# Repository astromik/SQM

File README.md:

<B>Amatérské SQM - Sky Quality Meter</B><br><br>Levnější a funkčně více vybavená náhrada za profesionální měřič kvality oblohy od Unihedronu postavená na procesoru STM32F411CEU s využitím modulu pro měření jasu TSL2591.

- Záznamy se ukládají na SD kartu (čitelný CSV formát) a do vnitřní EEPROM, ze které je možné záznamy exporovat.<br>
- Měření teploty, tlaku a vlhkosti.<br>
- K záznamům se přidávají GPS souřadnice a směr měření (azimut a  elevace).<br>
- Astronomické výpočty (poloha Slunce, Měsíce, planet, vybrané DSO).<br>
- Komunikace přes RS485 (modbus), nebo přes USB.<br>
- Možnost automatického měření v nastavených intervalech.<br>
- Další drobné funkce (stopky, budík, časová značka, červená lampička, GPX trasovací soubor).<br>
- Kalibrace pomocí porovnání s originálním (přesným) SQM přes editovatelné kalibrační tabulky.

Web: http://sqm.astromik.org/<br><br>

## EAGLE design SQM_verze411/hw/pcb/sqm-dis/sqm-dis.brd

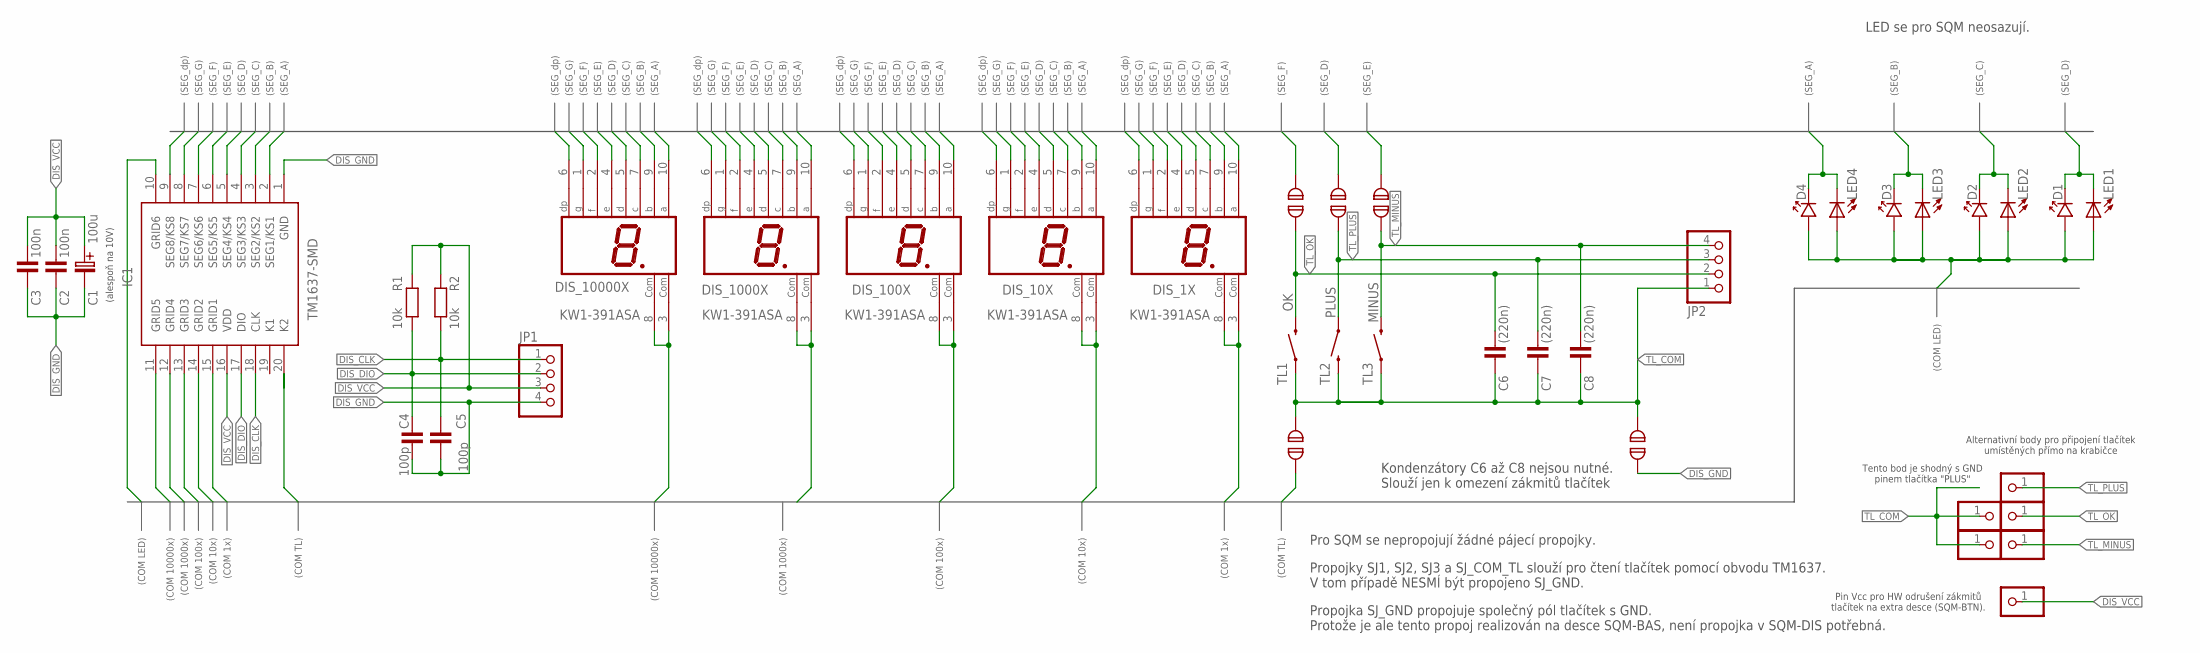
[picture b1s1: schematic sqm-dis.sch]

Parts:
C1: 100u; C-EL_2,5
C2, C3: 100n; 0805
C4, C5: 100p; 0805
C6, C7, C8: (220n); 0805
D1, D2, D3, D4: LED_3
DIS_1X, DIS_10X, DIS_100X, DIS_1000X, DIS_10000X: KW1-391ASA; HDSP-E
IC1: TM1637-SMD; SOIC127P1045X280-20N
JP1, JP2: PINHD-1X4; 1X04
JP3, JP4, JP5, JP6, JP7, JP8: PINHD-1X1; 1X01
LED1, LED2, LED3, LED4: LEDCHIP-LED0805; CHIP-LED0805
R1, R2: 10k; 0805
SJ1, SJ2, SJ3: SJ; SJ_2S-NO
SJ_COM_TL: SJ; SJ_2S-NO
SJ_GND: SJ; SJ_2S-NO
TL1: OK; TACTILE_SWITCH_PTH_6.0MM
TL2: PLUS; TACTILE_SWITCH_PTH_6.0MM
TL3: MINUS; TACTILE_SWITCH_PTH_6.0MM

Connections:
COM_BUS0: DIS_1X.3 (COM), DIS_1X.8 (COM), IC1.15 (GRID1)
COM_BUS1: DIS_10X.3 (COM), DIS_10X.8 (COM), IC1.14 (GRID2)
COM_BUS2: DIS_100X.3 (COM), DIS_100X.8 (COM), IC1.13 (GRID3)
COM_BUS3: DIS_1000X.3 (COM), DIS_1000X.8 (COM), IC1.12 (GRID4)
COM_BUS4: DIS_10000X.3 (COM), DIS_10000X.8 (COM), IC1.11 (GRID5)
COM_BUS5: IC1.20 (K2), SJ_COM_TL.1
COM_BUS6: D1.A, D2.A, D3.A, D4.A, IC1.10 (GRID6), LED1.A, LED2.A, LED3.A, LED4.A
DIS_CLK: C5.2, IC1.18 (CLK), JP1.1, R2.1
DIS_DIO: C4.2, IC1.17 (DIO), JP1.2, R1.1
DIS_GND: C1.C- (C_EL-), C2.1, C3.1, C4.1, C5.1, IC1.1 (GND), JP1.4, SJ_GND.1
DIS_VCC: C1.C+ (C_EL+), C2.2, C3.2, IC1.16 (VDD), JP1.3, JP3.1, R1.2, R2.2
SEG_BUS0: D4.K, DIS_1X.10 (A), DIS_10X.10 (A), DIS_100X.10 (A), DIS_1000X.10 (A), DIS_10000X.10 (A), IC1.2 (SEG1/KS1), LED4.C
SEG_BUS1: D3.K, DIS_1X.9 (B), DIS_10X.9 (B), DIS_100X.9 (B), DIS_1000X.9 (B), DIS_10000X.9 (B), IC1.3 (SEG2/KS2), LED3.C
SEG_BUS2: D2.K, DIS_1X.7 (C), DIS_10X.7 (C), DIS_100X.7 (C), DIS_1000X.7 (C), DIS_10000X.7 (C), IC1.4 (SEG3/KS3), LED2.C
SEG_BUS3: D1.K, DIS_1X.5 (D), DIS_10X.5 (D), DIS_100X.5 (D), DIS_1000X.5 (D), DIS_10000X.5 (D), IC1.5 (SEG4/KS4), LED1.C, SJ2.2
SEG_BUS4: DIS_1X.4 (E), DIS_10X.4 (E), DIS_100X.4 (E), DIS_1000X.4 (E), DIS_10000X.4 (E), IC1.6 (SEG5/KS5), SJ3.2
SEG_BUS5: DIS_1X.2 (F), DIS_10X.2 (F), DIS_100X.2 (F), DIS_1000X.2 (F), DIS_10000X.2 (F), IC1.7 (SEG6/KS6), SJ1.2
SEG_BUS6: DIS_1X.1 (G), DIS_10X.1 (G), DIS_100X.1 (G), DIS_1000X.1 (G), DIS_10000X.1 (G), IC1.8 (SEG7/KS7)
SEG_BUS7: DIS_1X.6 (DP), DIS_10X.6 (DP), DIS_100X.6 (DP), DIS_1000X.6 (DP), DIS_10000X.6 (DP), IC1.9 (SEG8/KS8)
TL_COM: C6.1, C7.1, C8.1, JP2.1, JP7.1, JP8.1, SJ_COM_TL.2, SJ_GND.2, TL1.1, TL2.3 (2), TL3.1
TL_MINUS: C8.2, JP2.4, JP6.1, SJ3.1, TL3.3 (2)
TL_OK: C6.2, JP2.2, JP4.1, SJ1.1, TL1.3 (2)
TL_PLUS: C7.2, JP2.3, JP5.1, SJ2.1, TL2.1

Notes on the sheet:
(SEG_A)
(SEG_B)
(SEG_C)
(SEG_D)
(SEG_E)
(SEG_F)
(SEG_G)
(SEG_dp)
(COM 10000x)
(COM 1000x)
(COM 100x)
(COM 10x)
(COM 1x)
(COM TL)
(COM LED)
Alternativní body pro připojení tlačítek umístěných přímo na krabičce
Tento bod je shodný s GND pinem tlačítka "PLUS"
(alespoň na 10V)
Pro SQM se nepropojují žádné pájecí propojky.
Propojky SJ1, SJ2, SJ3 a SJ_COM_TL slouží pro čtení tlačítek pomocí obvodu TM1637. V tom případě NESMÍ být propojeno SJ_GND.
Propojka SJ_GND propojuje společný pól tlačítek s GND. Protože je ale tento propoj realizován na desce SQM-BAS, není propojka v SQM-DIS potřebná.
Kondenzátory C6 až C8 nejsou nutné. Slouží jen k omezení zákmitů tlačítek
LED se pro SQM neosazují.
Pin Vcc pro HW odrušení zákmitů tlačítek na extra desce (SQM-BTN).

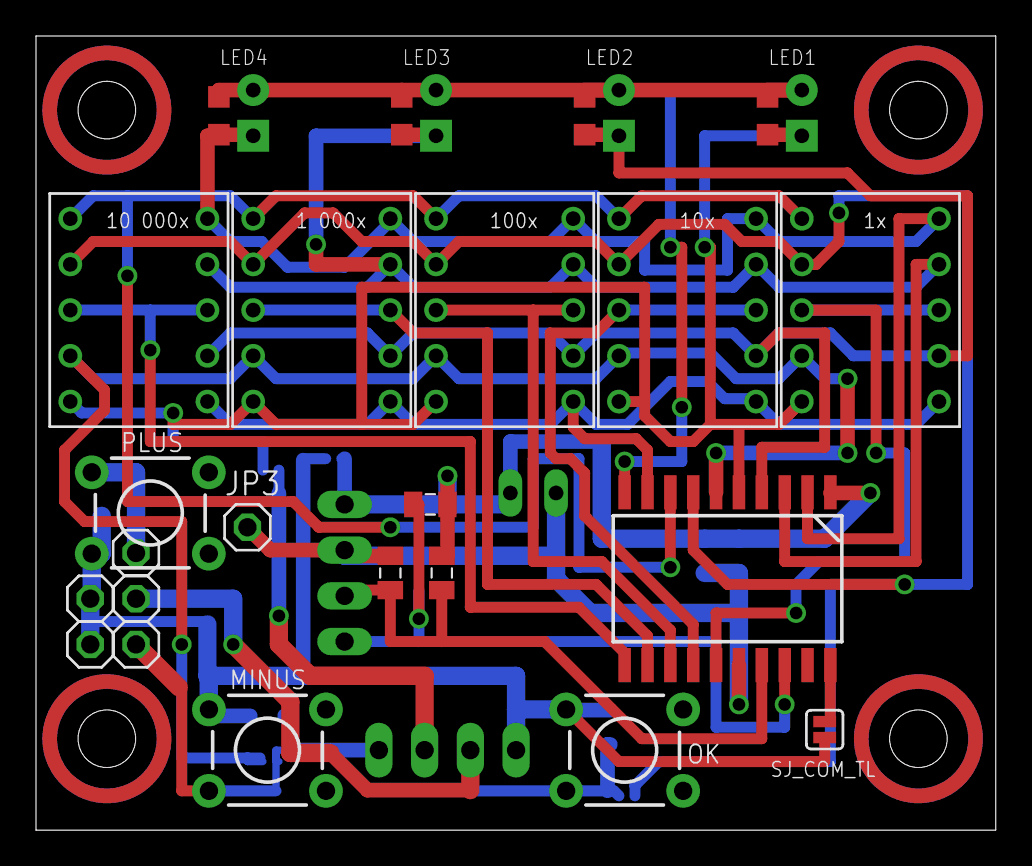
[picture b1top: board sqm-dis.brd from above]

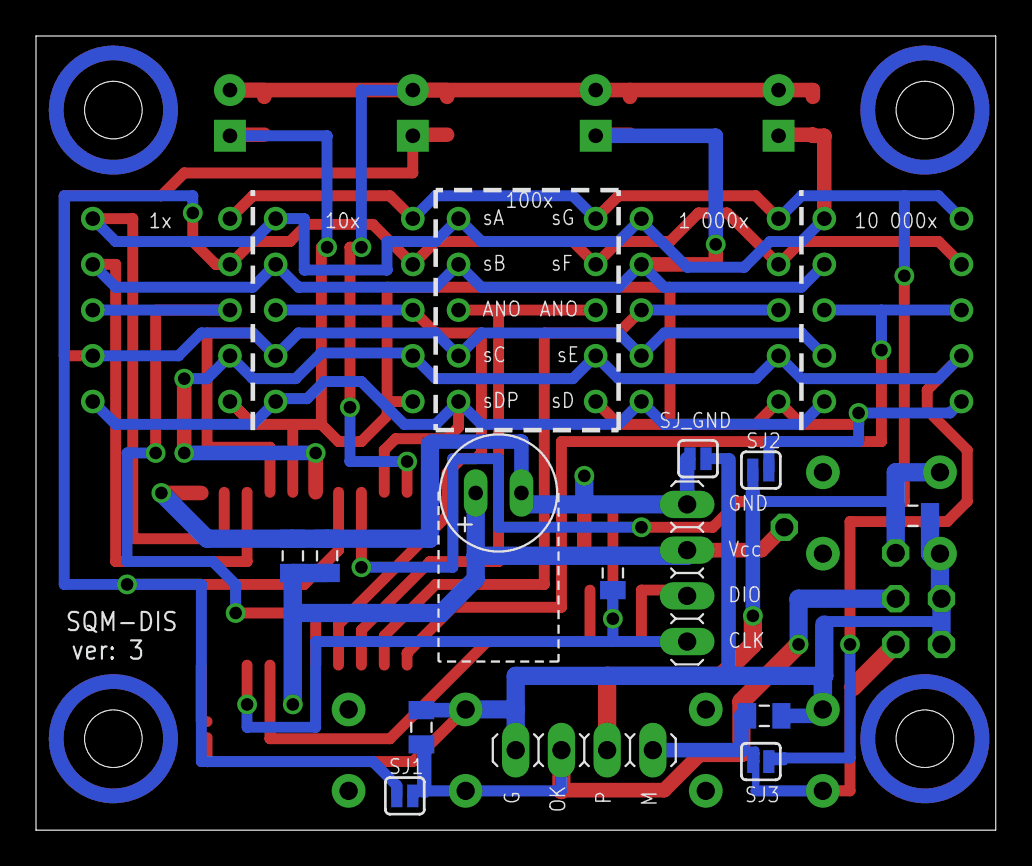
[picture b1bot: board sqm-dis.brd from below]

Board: 2 copper layers, 53.3 x 44.1 mm, 40 parts (13 on the bottom side), 23 nets.

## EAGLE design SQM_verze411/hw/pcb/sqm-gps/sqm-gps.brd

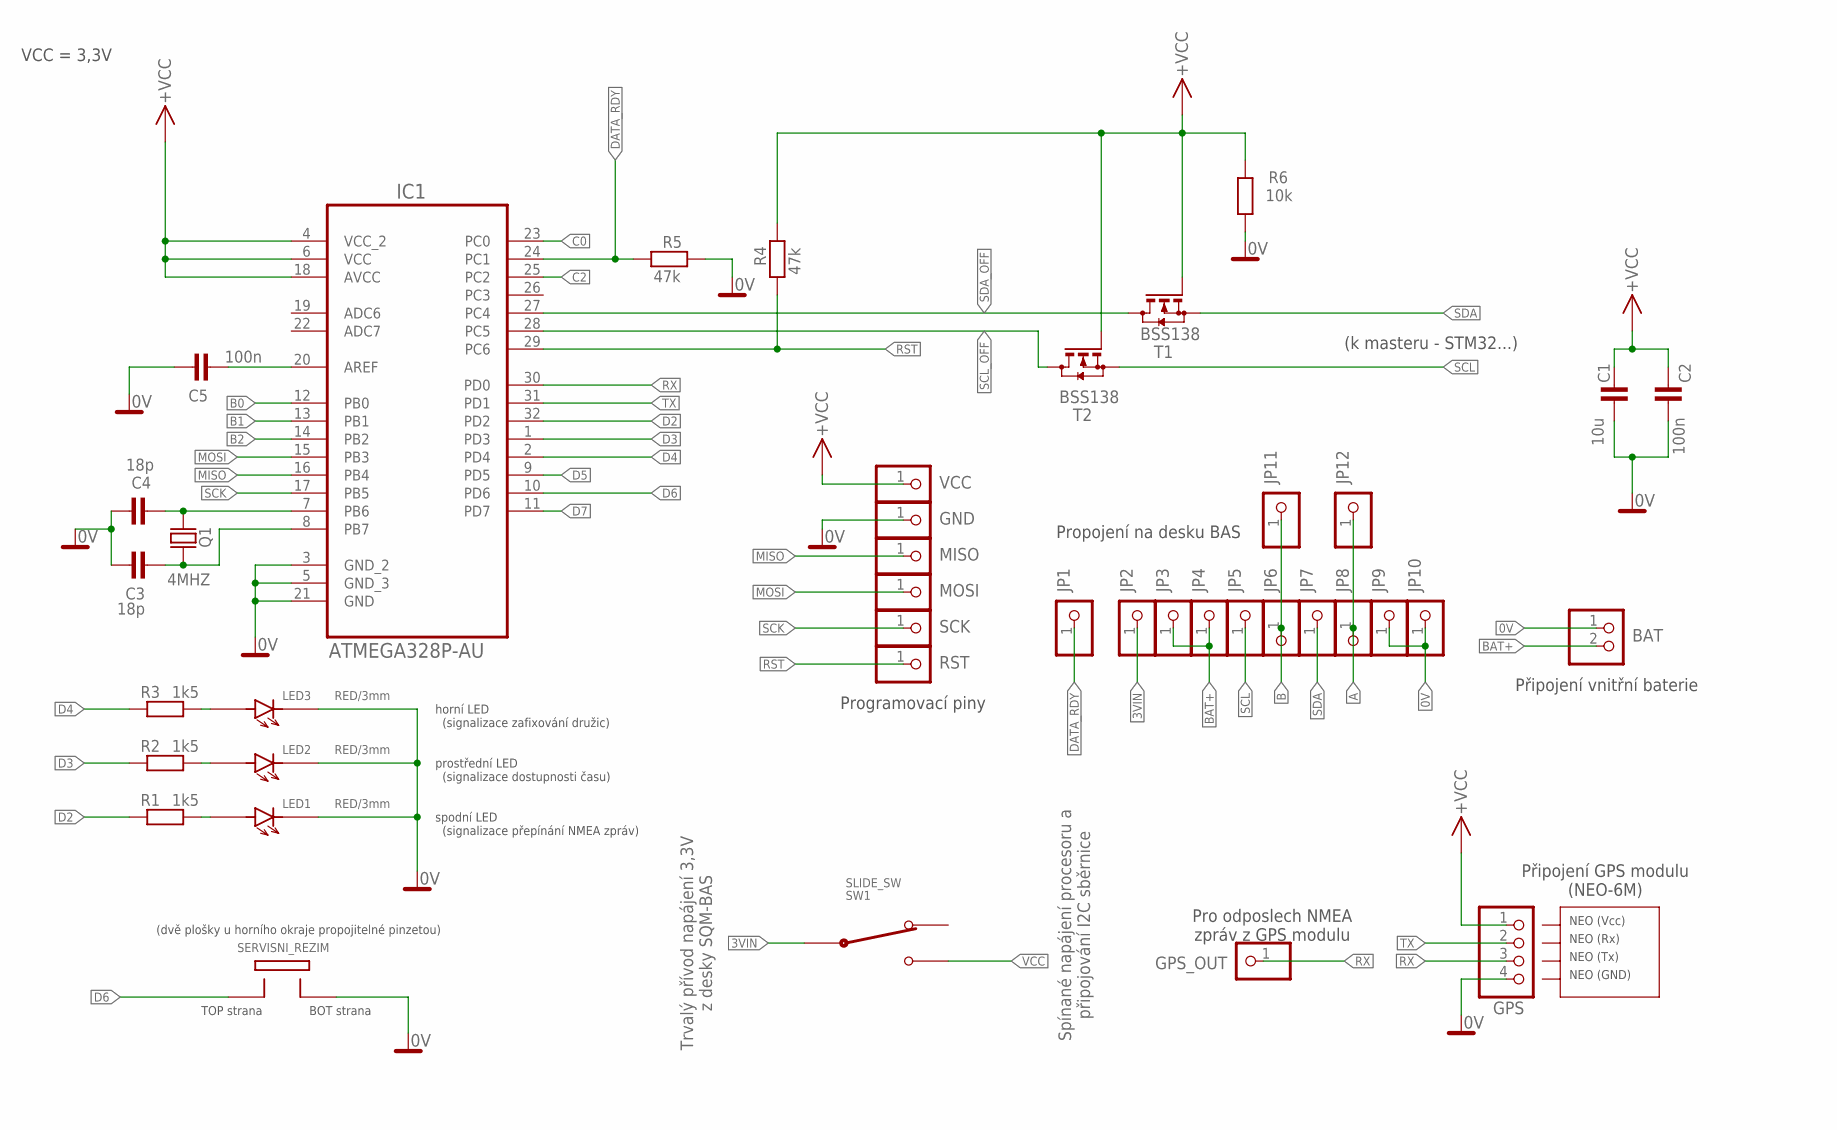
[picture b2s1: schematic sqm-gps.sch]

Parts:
BAT: PINHD-1X2; 1X02
C1: 10u; 1206
C2, C5: 100n; 0805
C3, C4: 18p; 0805
GND: PINHD-1X1; 1X01
GPS: PINHD-1X4; 1X04
GPS_OUT: PINHD-1X1; 1X01
IC1: ATMEGA328P-AU; QFP80P900X900X120-32N
JP1, JP2, JP3, JP4, JP5, JP6, JP7, JP8, JP9, JP10, JP11, JP12: PINHD-1X1; 1X01
LED1, LED2, LED3: RED/3mm; LED3MM_BOK
MISO: PINHD-1X1; 1X01
MOSI: PINHD-1X1; 1X01
Q1: 4MHZ; HC-49U
R1, R2, R3: 1k5; 0805
R4, R5: 47k; 0805
R6: 10k; 0805
RST: PINHD-1X1; 1X01
SCK: PINHD-1X1; 1X01
SERVISNI_REZIM: TOP_BOT_PIN
SW1: SLIDE_SW
T1, T2: BSS138; SOT23
VCC: PINHD-1X1; 1X01

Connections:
0V: BAT.1, C1.2, C2.1, C3.2, C4.1, C5.2, GND.1, GPS.4, IC1.3 (GND_2), IC1.5 (GND_3), IC1.21 (GND), JP9.1, JP10.1, LED1.K, LED2.K, LED3.K, R5.2, R6.1, SERVISNI_REZIM.P2
3VIN: JP2.1, SW1.PIN_COM
A: JP8.1, JP12.1
AREF: C5.1, IC1.20 (AREF)
B: JP6.1, JP11.1
B0: IC1.12 (PB0)
B1: IC1.13 (PB1)
B2: IC1.14 (PB2)
B6: C4.2, IC1.7 (PB6), Q1.2
B7: C3.1, IC1.8 (PB7), Q1.1
BAT+: BAT.2, JP3.1, JP4.1
C0: IC1.23 (PC0)
C2: IC1.25 (PC2)
D2: IC1.32 (PD2), R1.1
D3: IC1.1 (PD3), R2.1
D4: IC1.2 (PD4), R3.1
D5: IC1.9 (PD5)
D6: IC1.10 (PD6), SERVISNI_REZIM.P1
D7: IC1.11 (PD7)
DATA_RDY: IC1.24 (PC1), JP1.1, R5.1
LED1_A1: LED1.A, R1.2
LED2_A1: LED2.A, R2.2
LED3_A1: LED3.A, R3.2
MISO: IC1.16 (PB4), MISO.1
MOSI: IC1.15 (PB3), MOSI.1
RST: IC1.29 (PC6), R4.1, RST.1
RX: GPS.3, GPS_OUT.1, IC1.30 (PD0)
SCK: IC1.17 (PB5), SCK.1
SCL: JP5.1, T2.2 (S)
SCL_OFF: IC1.28 (PC5), T2.3 (D)
SDA: JP7.1, T1.2 (S)
SDA_OFF: IC1.27 (PC4), T1.3 (D)
TX: GPS.2, IC1.31 (PD1)
VCC: C1.1, C2.2, GPS.1, IC1.4 (VCC_2), IC1.6 (VCC), IC1.18 (AVCC), R4.2, R6.2, SW1.PIN_2, T1.1 (G), T2.1 (G), VCC.1

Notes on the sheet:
Propojení na desku BAS
Připojení vnitřní baterie
Programovací piny
Připojení GPS modulu (NEO-6M)
Trvalý přívod napájení 3,3V z desky SQM-BAS
Spínané napájení procesoru a připojování I2C sběrnice
(k masteru - STM32...)
spodní LED (signalizace přepínání NMEA zpráv)
prostřední LED (signalizace dostupnosti času)
horní LED (signalizace zafixování družic)
TOP strana
BOT strana
VCC = 3,3V
(dvě plošky u horního okraje propojitelné pinzetou)
NEO (Rx)
NEO (Tx)
NEO (GND)
NEO (Vcc)
Pro odposlech NMEA zpráv z GPS modulu

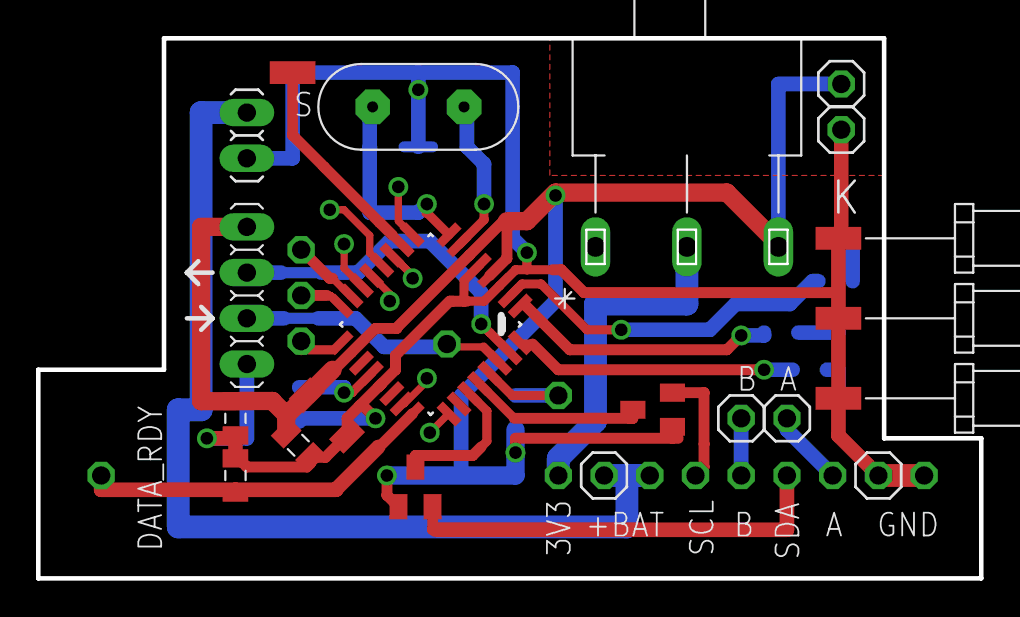
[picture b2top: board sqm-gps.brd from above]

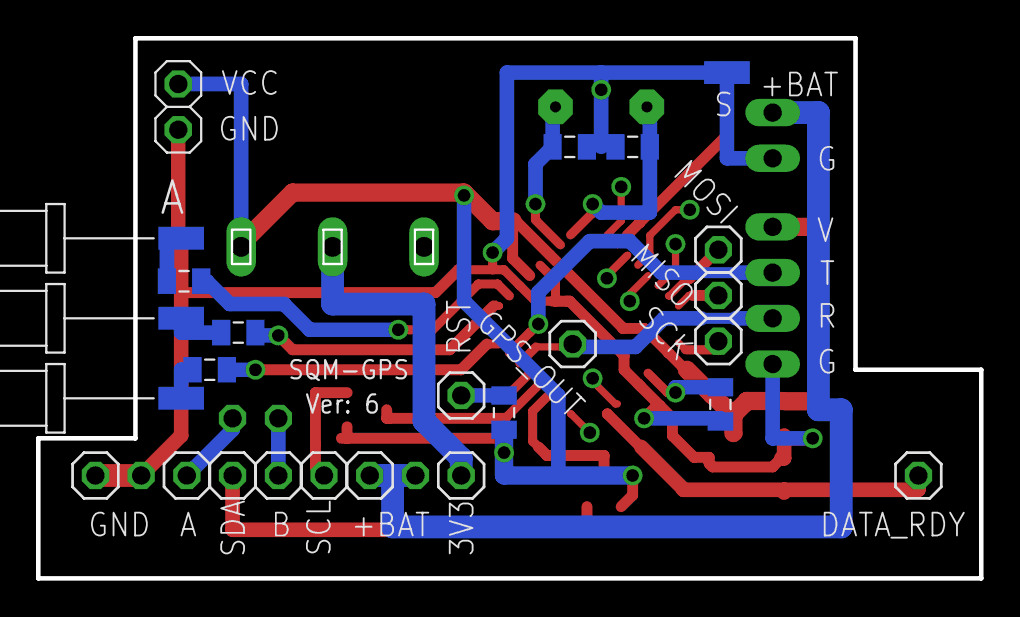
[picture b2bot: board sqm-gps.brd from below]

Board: 2 copper layers, 52.4 x 30.0 mm, 41 parts (20 on the bottom side), 27 nets.

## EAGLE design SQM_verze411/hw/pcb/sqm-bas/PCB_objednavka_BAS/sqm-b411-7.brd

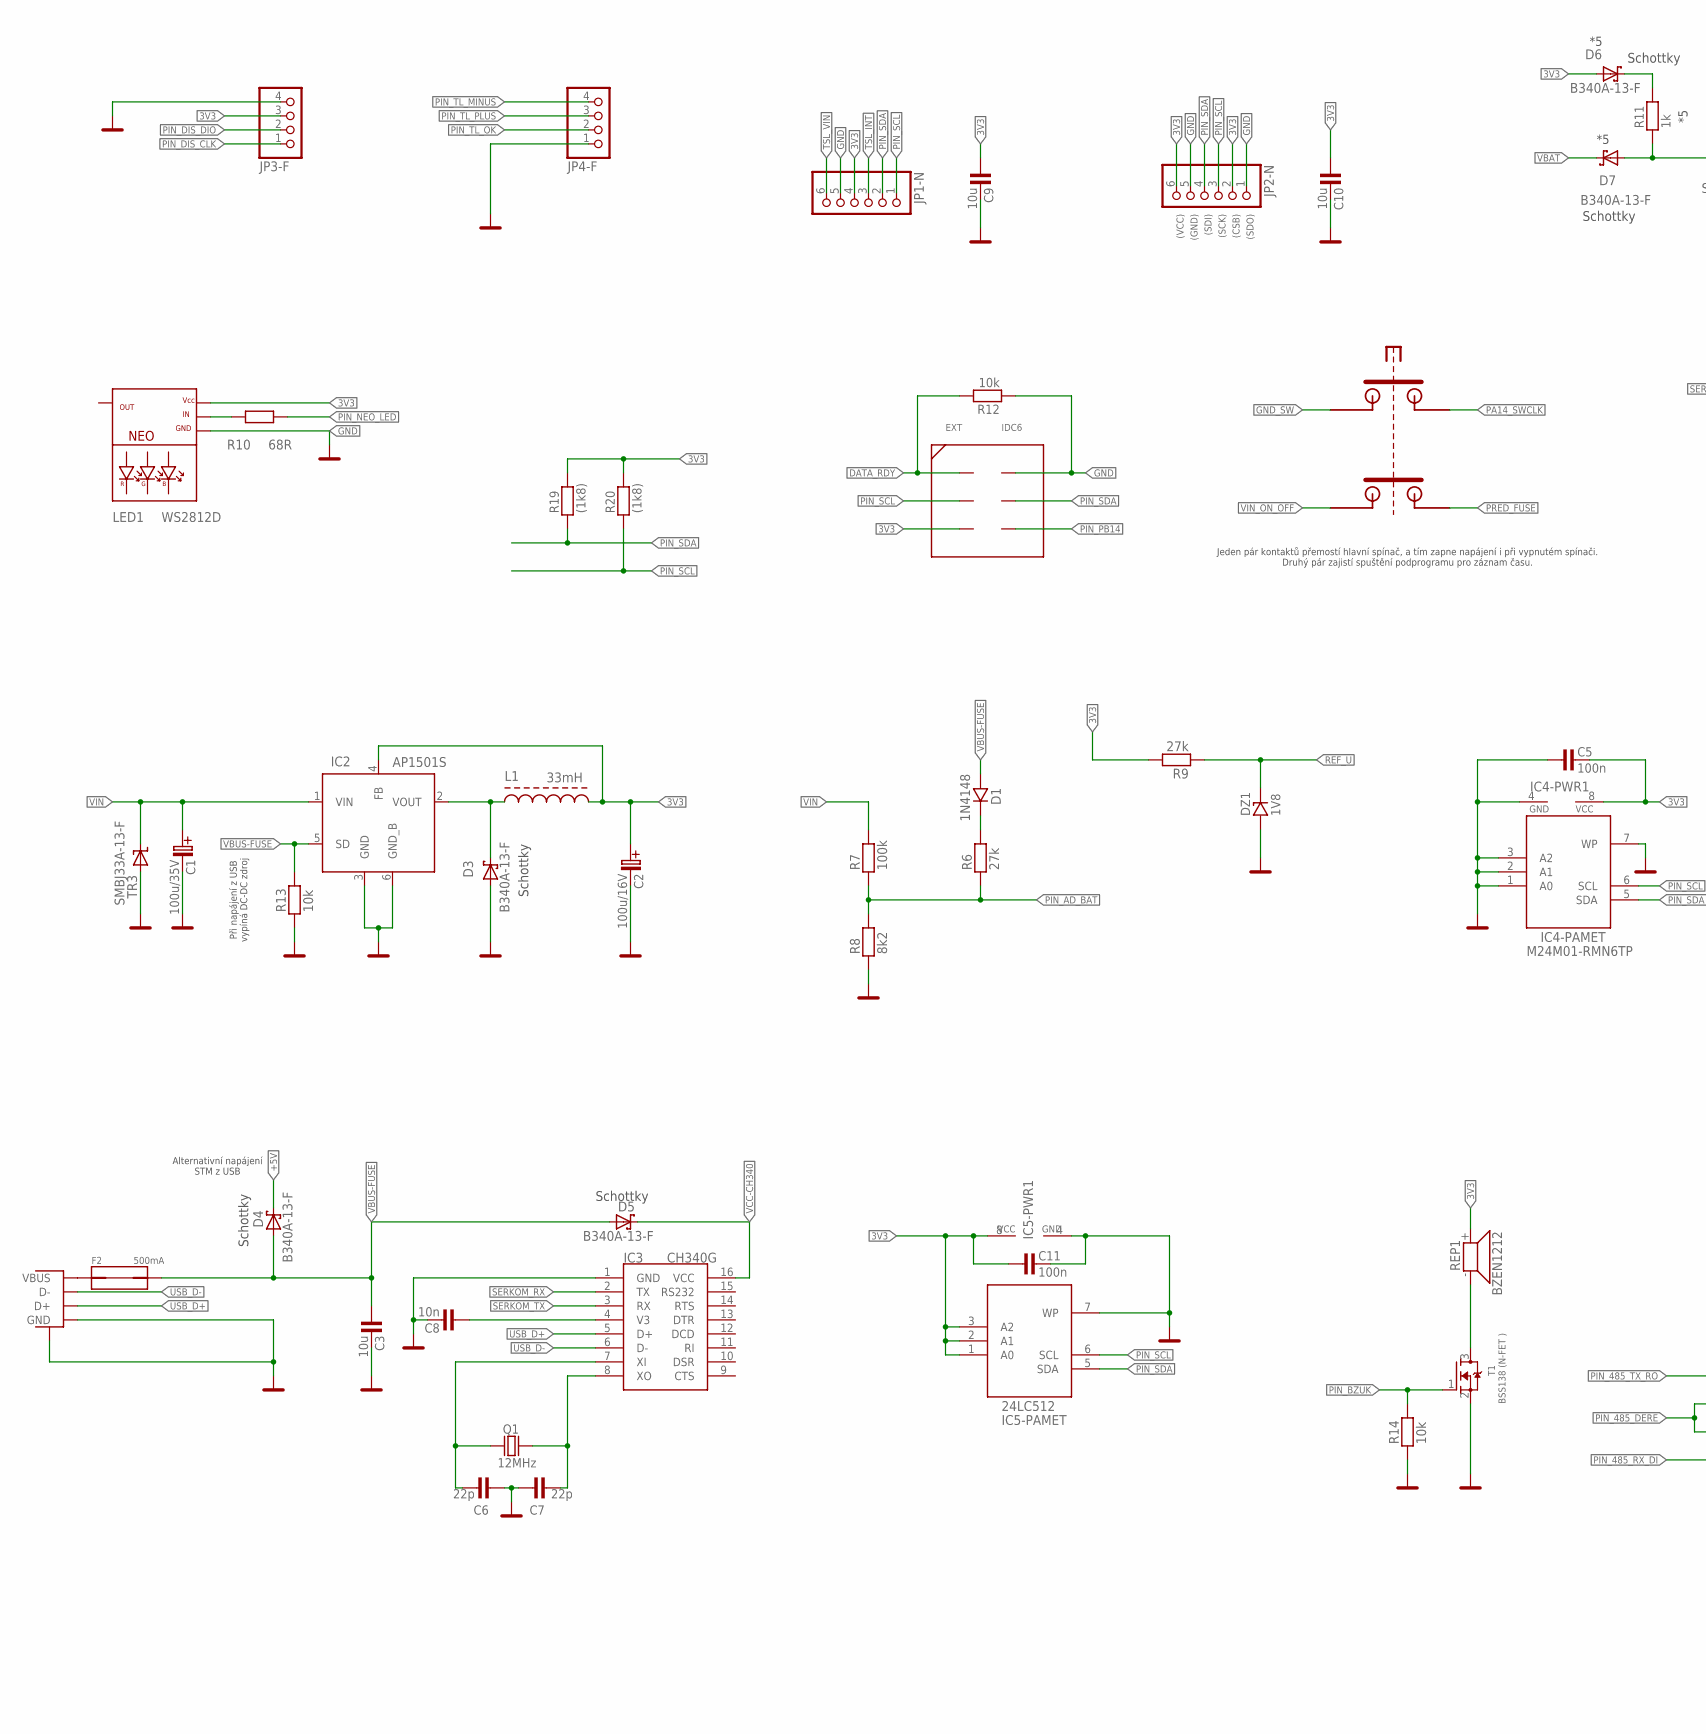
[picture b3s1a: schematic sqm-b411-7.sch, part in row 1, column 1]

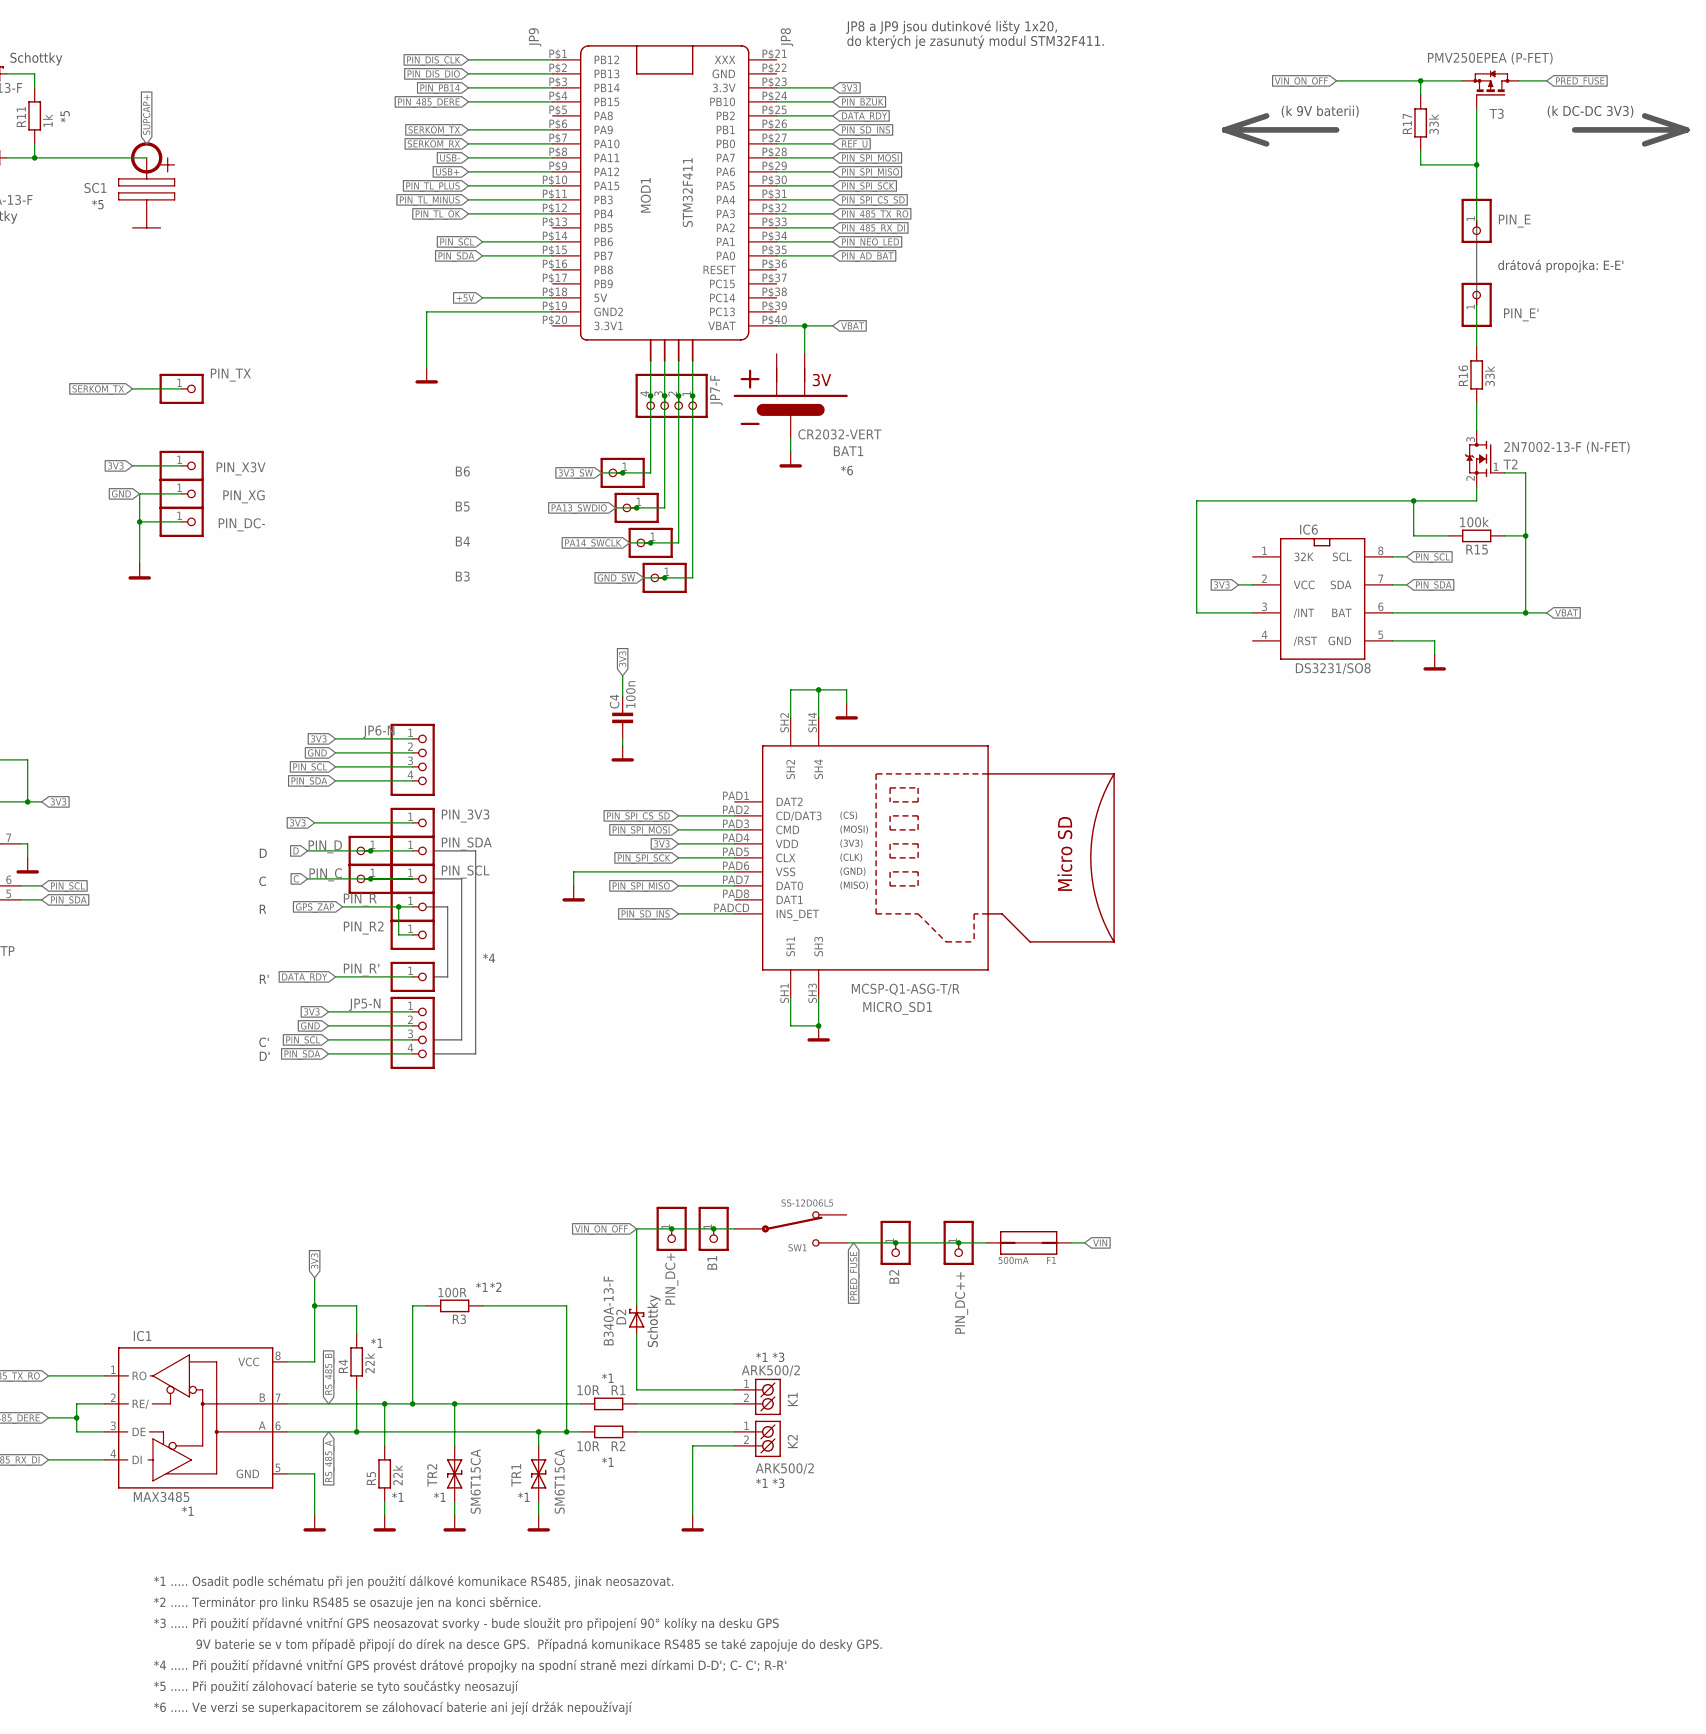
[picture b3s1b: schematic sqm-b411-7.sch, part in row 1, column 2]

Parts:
B1, B2, B3, B4, B5, B6: PINHD-1X1; 1X01
BAT1: CR2032-VERT
C1: 100u/35V; C-EL_3,5
C2: 100u/16V; C-EL_3,5
C3, C9, C10: 10u; 0805
C4, C5, C11: 100n; 0805
C6, C7: 22p; 0805
C8: 10n; 0805
D1: 1N4148; SOD-80
D2, D3, D4, D5, D6, D7: B340A-13-F; SMB
DZ1: 1V8; SOD-80
EXT: IDC6
F1, F2: 500mA; FUSE1812
IC1: MAX3485; SO08
IC2: AP1501S; TO263-5
IC3: CH340G; SOIC16
IC4: M24M01-RMN6TP; SO8
IC5: 24LC512; SO8
IC6: DS3231/SO8; SO8
JP1-N, JP2-N: PINHD-1X6; 1X06
JP3-F, JP4-F, JP5-N, JP6-N, JP7-F: PINHD-1X4; 1X04
K1, K2: ARK500/2
L1: 33mH; SMD_INDUCTOR
LED1: WS2812D; LED_5-RGB
MICRO_SD1: MCSP-Q1-ASG-T/R; MICRO_SD
MOD1: STM32F411; BLACK411_PILL
PIN_3V3: PINHD-1X1; 1X01
PIN_C: PINHD-1X1; 1X01
PIN_D: PINHD-1X1; 1X01
PIN_DC+: PINHD-1X1; 1X01
PIN_DC++: PINHD-1X1; 1X01
PIN_DC-: PINHD-1X1; 1X01
PIN_E: PINHD-1X1; 1X01
PIN_E': PINHD-1X1; 1X01
PIN_R, PIN_R2: PINHD-1X1; 1X01
PIN_R': PINHD-1X1; 1X01
PIN_SCL: PINHD-1X1; 1X01
PIN_SDA: PINHD-1X1; 1X01
PIN_TX: PINHD-1X1; 1X01
PIN_X3V: PINHD-1X1; 1X01
PIN_XG: PINHD-1X1; 1X01
Q1: 12MHz; HC-49U
R1, R2: 10R; 1206
R3: 100R; 0805
R4, R5: 22k; 0805
R6, R9: 27k; 0805
R7, R15: 100k; 0805
R8: 8k2; 0805
R10: 68R; 0805
R11: 1k; 0805
R12, R13, R14: 10k; 0805
R16, R17: 33k; 0805
R19, R20: (1k8); 0805
REP1: BZEN1212; KPE242
SUPCAP-DIRA: DIRA
SW1: SS-12D06L5; SLIDE_SW
T1: BSS138 (N-FET ); SOT23
T2: 2N7002-13-F (N-FET); SOT23
T3: PMV250EPEA (P-FET); SOT23
TR1, TR2: SM6T15CA; SMBJ
TR3: SMBJ33A-13-F; SMBJ
USB1: USBPTH; USB-B-PTH

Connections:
3V3: C2.C+ (C_EL+), C4.2, C5.2, C9.1, C10.1, C11.1, D6.A, EXT.P5 (PIN5), IC1.8 (VCC), IC2.4 (FB), IC4.8 (VCC), IC5.1 (A0), IC5.2 (A1), IC5.3 (A2), IC5.8 (VCC), IC6.2 (VCC), JP1-N.4, JP2-N.2, JP2-N.6, JP3-F.3, JP5-N.1, JP6-N.1, L1.P$2, LED1.V (VCC), MICRO_SD1.PAD4 (VDD), MOD1.P$23 (3.3V), PIN_3V3.1, PIN_X3V.1, R4.2, R9.2, R19.2, R20.2, REP1.+
3V3_SW: B6.1, JP7-F.4
+5V: D4.C, MOD1.P$18 (5V)
BZUK_DRAIN: REP1.-, T1.3 (D)
C: PIN_C.1, PIN_SCL.1
CH340-V3: C8.1, IC3.4 (V3)
CHARGE: D6.C, R11.2
D: PIN_D.1, PIN_SDA.1
D2-R6: D1.K, R6.2
DATA_RDY: EXT.P1 (PIN1), MOD1.P$25 (PB2), PIN_R'.1, R12.2
DCDC-SW: D3.C, IC2.2 (VOUT), L1.P$1
E: PIN_E.1, R17.1, T3.1 (G)
E'': PIN_E'.1, R16.2
GND: BAT1.MINUS, C1.C- (C_EL-), C2.C- (C_EL-), C3.2, C4.1, C5.1, C6.1, C7.2, C8.2, C9.2, C10.2, C11.2, D3.A, DZ1.A, EXT.P2 (PIN2), IC1.5 (GND), IC2.3 (GND), IC2.6 (GND_B), IC3.1 (GND), IC4.1 (A0), IC4.2 (A1), IC4.3 (A2), IC4.4 (GND), IC4.7 (WP), IC5.4 (GND), IC5.7 (WP), IC6.5 (GND), JP1-N.5, JP2-N.1, JP2-N.5, JP3-F.4, JP4-F.1, JP5-N.2, JP6-N.2, K2.2 (K2), LED1.G (GND), MICRO_SD1.PAD6 (VSS), MICRO_SD1.SH1, MICRO_SD1.SH2, MICRO_SD1.SH3, MICRO_SD1.SH4, MOD1.P$19 (GND2), PIN_DC-.1, PIN_XG.1, R5.1, R8.1, R12.1, R13.1, R14.1, T1.2 (S), TR1.A, TR2.A, TR3.A, USB1.GND, USB1.P$2 (SHIELD)
GND_SW: B3.1, JP7-F.1
GPS_ZAP: PIN_R.1, PIN_R2.1
LED_RK: LED1.I (IN), R10.1
PA13_SWDIO: B5.1, JP7-F.3
PA14_SWCLK: B4.1, JP7-F.2
PIN_485_DERE: IC1.2 (RE/), IC1.3 (DE), MOD1.P$4 (PB15)
PIN_485_RX_DI: IC1.4 (DI), MOD1.P$33 (PA2)
PIN_485_TX_RO: IC1.1 (RO), MOD1.P$32 (PA3)
PIN_AD_BAT: MOD1.P$35 (PA0), R6.1, R7.1, R8.2
PIN_BZUK: MOD1.P$24 (PB10), R14.2, T1.1 (G)
PIN_DIS_CLK: JP3-F.1, MOD1.P$1 (PB12)
PIN_DIS_DIO: JP3-F.2, MOD1.P$2 (PB13)
PIN_NEO_LED: MOD1.P$34 (PA1), R10.2
PIN_PB14: EXT.P6 (PIN6), MOD1.P$3 (PB14)
PIN_SCL: EXT.P3 (PIN3), IC4.6 (SCL), IC5.6 (SCL), IC6.8 (SCL), JP1-N.1, JP2-N.3, JP5-N.3, JP6-N.3, MOD1.P$14 (PB6), R20.1
PIN_SDA: EXT.P4 (PIN4), IC4.5 (SDA), IC5.5 (SDA), IC6.7 (SDA), JP1-N.2, JP2-N.4, JP5-N.4, JP6-N.4, MOD1.P$15 (PB7), R19.1
PIN_SD_INS: MICRO_SD1.PADCD (INS_DET), MOD1.P$26 (PB1)
PIN_SPI_CS_SD: MICRO_SD1.PAD2 (CD/DAT3), MOD1.P$31 (PA4)
PIN_SPI_MISO: MICRO_SD1.PAD7 (DAT0), MOD1.P$29 (PA6)
PIN_SPI_MOSI: MICRO_SD1.PAD3 (CMD), MOD1.P$28 (PA7)
PIN_SPI_SCK: MICRO_SD1.PAD5 (CLX), MOD1.P$30 (PA5)
PIN_TL_MINUS: JP4-F.4, MOD1.P$11 (PB3)
PIN_TL_OK: JP4-F.2, MOD1.P$12 (PB4)
PIN_TL_PLUS: JP4-F.3, MOD1.P$10 (PA15)
PRED_FUSE: B2.1, F1.P$1, PIN_DC++.1, SW1.PIN_2, T3.3 (D)
REF_U: DZ1.K, MOD1.P$27 (PB0), R9.1
RS485-A-IN: K2.1 (K1), R2.1
RS485-B-IN: K1.2 (K2), R1.1
RS_485_A: IC1.6 (A), R2.2, R3.1, R4.1, TR1.C
RS_485_B: IC1.7 (B), R1.2, R3.2, R5.2, TR2.C
RTC_INT: IC6.3 (/INT), R15.2, T2.2 (S)
SERKOM_RX: IC3.2 (TX), MOD1.P$7 (PA10)
SERKOM_TX: IC3.3 (RX), MOD1.P$6 (PA9), PIN_TX.1
SUPCAP+: D7.A, R11.1, SUPCAP-DIRA.P$1
T2_DRAIN: R16.1, T2.3 (D)
TSL_INT: JP1-N.3
TSL_VIN: JP1-N.6
UBAT: D2.A, K1.1 (K1)
USB+: MOD1.P$9 (PA12)
USB-: MOD1.P$8 (PA11)
USB_D+: IC3.5 (D+), USB1.D+
USB_D-: IC3.6 (D-), USB1.D-
V-USB-IN: F2.P$2, USB1.VBUS
VBAT: BAT1.PLUS2, D7.C, IC6.6 (BAT), MOD1.P$40 (VBAT), R15.1, T2.1 (G)
VBUS-FUSE: C3.1, D1.A, D4.A, D5.A, F2.P$1, IC2.5 (SD), R13.2
VCC-CH340: D5.C, IC3.16 (VCC)
VIN: C1.C+ (C_EL+), F1.P$2, IC2.1 (VIN), R7.2, TR3.C
VIN_ON_OFF: B1.1, D2.C, PIN_DC+.1, R17.2, SW1.PIN_COM, T3.2 (S)
XI: C6.2, IC3.7 (XI), Q1.1
XO: C7.1, IC3.8 (XO), Q1.2
XXX: MOD1.P$21 (XXX)

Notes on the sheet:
(SDO)
(CSB)
(SCK)
(SDI)
(GND)
(VCC)
Schottky
Alternativní napájení STM z USB
Při napájení z USB vypíná DC-DC zdroj
SC1
Jeden pár kontaktů přemostí hlavní spínač, a tím zapne napájení i při vypnutém spínači. Druhý pár zajistí spuštění podprogramu pro záznam času.
*1 *3
*1 ..... Osadit podle schématu při jen použití dálkové komunikace RS485, jinak neosazovat.
*3 ..... Při použití přídavné vnitřní GPS neosazovat svorky - bude sloužit pro připojení 90° kolíky na desku GPS
*4 ..... Při použití přídavné vnitřní GPS provést drátové propojky na spodní straně mezi dírkami D-D'; C- C'; R-R'
drátová propojka: E-E'
*2 ..... Terminátor pro linku RS485 se osazuje jen na konci sběrnice.
9V baterie se v tom případě připojí do dírek na desce GPS. Případná komunikace RS485 se také zapojuje do desky GPS.
JP8
JP9
JP8 a JP9 jsou dutinkové lišty 1x20, do kterých je zasunutý modul STM32F411.
*5 ..... Při použití zálohovací baterie se tyto součástky neosazují
*6 ..... Ve verzi se superkapacitorem se zálohovací baterie ani její držák nepoužívají
(k 9V baterii)
(k DC-DC 3V3)

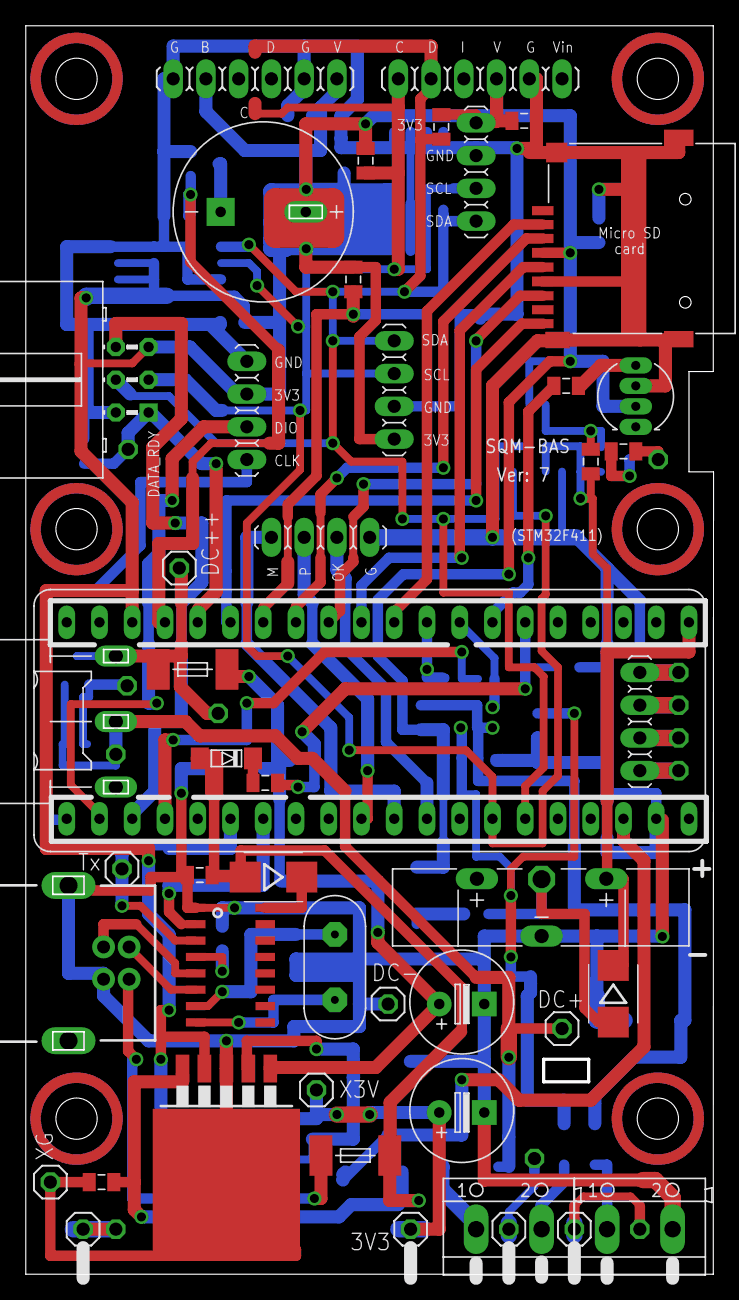
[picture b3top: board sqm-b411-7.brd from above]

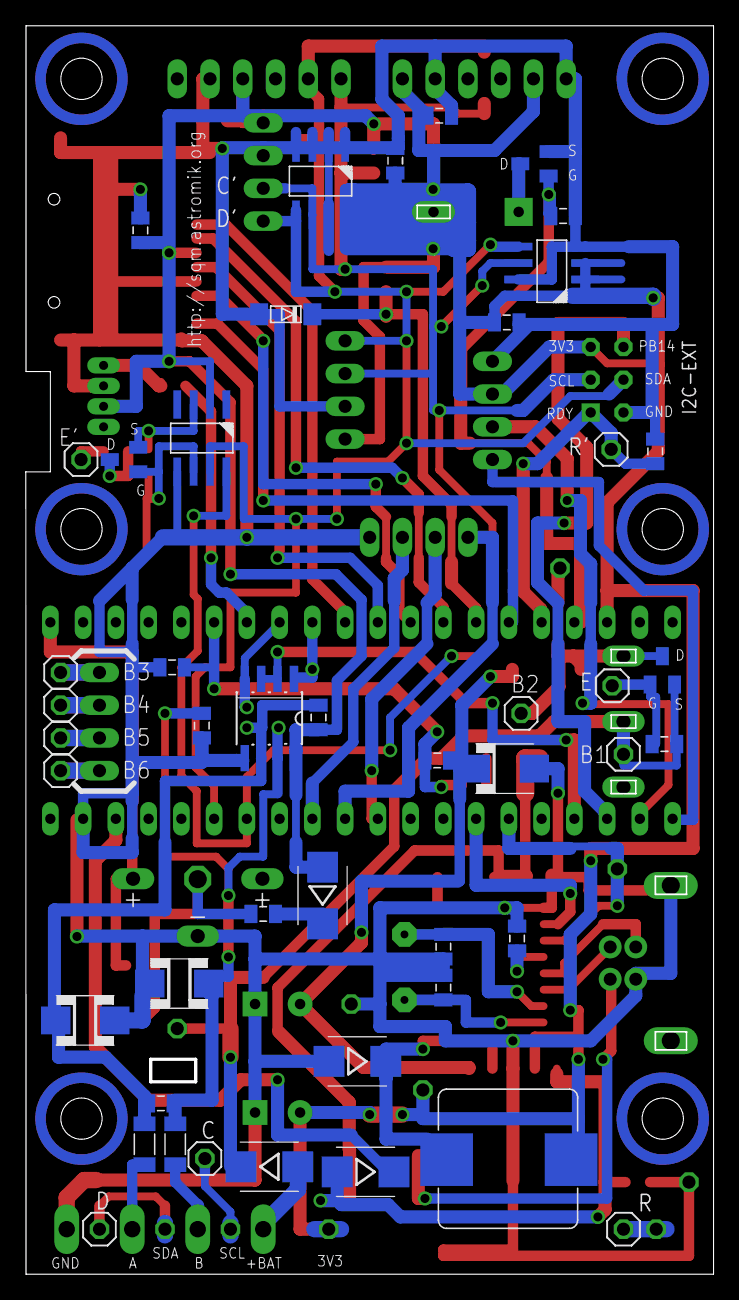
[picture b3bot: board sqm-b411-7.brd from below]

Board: 2 copper layers, 53.1 x 96.6 mm, 94 parts (46 on the bottom side), 60 nets.

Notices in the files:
parts and their libraries:
Copyright (C) PaJa 2011
Copyright (C) PaJa 2001-2014
SparkFun-Switches: Licensing: Creative Commons ShareAlike 4.0 International - https://creativecommons.org/licenses/by-sa/4.0
Copyright (C) PaJa 2001-2011
